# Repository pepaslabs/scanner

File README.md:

# Scanner

This ia a relay board for scanning voltage references.

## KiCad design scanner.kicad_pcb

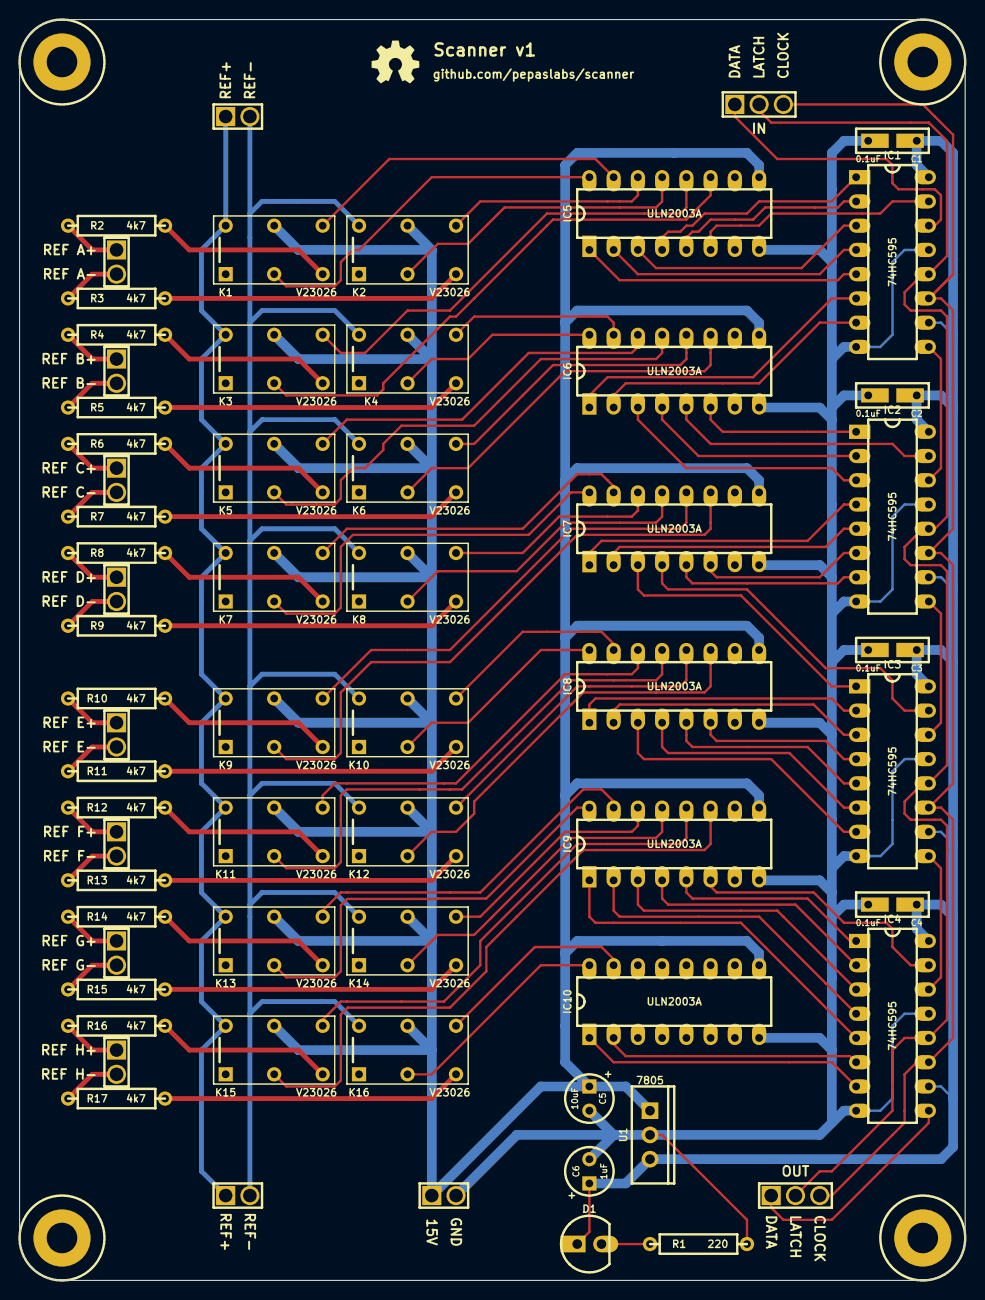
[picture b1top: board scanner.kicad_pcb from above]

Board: 2 copper layers, 99.1 x 132.1 mm, 68 parts (0 on the bottom side), 109 nets.

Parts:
C1, C2, C3, C4: 0.1uF; PL_ANYSSCAP_SMALL_2_059B_0805
C5: 10uF; PL_ELCAP_10_20_V_059A
C6: 1uF; PL_ELCAP_10_20_V_059A
D1: LED; PL_LED_5MM
H***: Val**; PL_hole_M3
H***#2, H***#3, H***#4: Val**; PL_hole_M3
IC1, IC2, IC3, IC4: 74HC595; PL_DIP16
IC5, IC6, IC7, IC8, IC9, IC10: ULN2003A; PL_DIP16
K1, K2, K3, K4, K5, K6, K7, K8, K9, K10, K11, K12, K13, K14, K15, K16: V23026; PL_V23026
P1, P3, P4, P5, P6, P7, P8, P9, P10, P11, P13: CONN_2X1; PL_SIL-2-MCHN
P2, P12: CONN_3X1; PL_SIL-3-MCHN
R1: 220; PL_R_AXIAL_0W25_059A
R2, R3, R4, R5, R6, R7, R8, R9, R10, R11, R12, R13, R14, R15, R16, R17: 4k7; PL_R_AXIAL_0W25_059A
U1: 7805; PL_TO-220_V_069A

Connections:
5V: C1.1, C2.1, C3.1, C4.1, C6.1, D1.1, IC1.10, IC1.16, IC2.10, IC2.16, IC3.10, IC3.16, IC4.10, IC4.16, U1.3
15V: C5.1, IC5.9, IC6.9, IC7.9, IC8.9, IC9.9, IC10.9, K1.5, K2.5, K3.5, K4.5, K5.5, K6.5, K7.5, K8.5, K9.5, K10.5, K11.5, K12.5, K13.5, K14.5, K15.5, K16.5, P1.1, U1.1
CLOCK: IC1.11, IC2.11, IC3.11, IC4.11, P2.3, P12.3
DATA: IC1.14, P2.1
DATA OUT: IC4.9, P12.1
GND: C1.2, C2.2, C3.2, C4.2, C5.2, C6.2, IC1.8, IC1.13, IC2.8, IC2.13, IC3.8, IC3.13, IC4.8, IC4.13, IC5.8, IC6.8, IC7.8, IC8.8, IC9.8, IC10.8, P1.2, R1.2, U1.2
LATCH: IC1.12, IC2.12, IC3.12, IC4.12, P2.2, P12.2
unnamed: IC8.16, K10.2
unnamed: IC7.13, K8.2
unnamed: IC7.12, K9.4
unnamed: IC7.14, K8.4
unnamed: IC8.15, K10.4
unnamed: IC8.14, K11.4
unnamed: IC8.13, K11.2
unnamed: IC8.12, K12.4
unnamed: IC6.16, K4.2
unnamed: IC6.15, K4.4
unnamed: IC6.14, K5.4
unnamed: IC6.13, K5.2
unnamed: IC6.12, K6.4
unnamed: IC7.16, K7.2
unnamed: IC7.15, K7.4
unnamed: IC9.12, K15.4
unnamed: IC9.16, K13.2
unnamed: IC9.15, K13.4
unnamed: IC9.14, K14.4
unnamed: IC10.16, K16.2
unnamed: IC10.15, K16.4
unnamed: IC5.14, K2.4
unnamed: IC5.16, K1.2
unnamed: IC5.15, K1.4
unnamed: IC5.13, K2.2
unnamed: IC5.12, K3.4
unnamed: P3.1, R2.1
unnamed: P3.2, R3.1
unnamed: D1.2, R1.1
unnamed: IC9.11, K15.2
unnamed: P4.1, R4.1
unnamed: P4.2, R5.1
unnamed: P5.1, R6.1
unnamed: P5.2, R7.1
unnamed: IC9.13, K14.2
unnamed: P6.1, R8.1
unnamed: P6.2, R9.1
unnamed: IC5.11, K3.2
unnamed: IC6.11, K6.2
unnamed: IC7.11, K9.2
unnamed: IC8.11, K12.2
unnamed: P9.1, R14.1
unnamed: P9.2, R15.1
unnamed: P10.1, R16.1
unnamed: P10.2, R17.1
unnamed: P8.2, R13.1
unnamed: P7.1, R10.1
unnamed: P7.2, R11.1
unnamed: P8.1, R12.1
unnamed: IC1.9, IC2.14
unnamed: IC2.9, IC3.14
unnamed: IC3.9, IC4.14
REF A+: K1.3, R2.2
REF A+ DIS: IC1.5, IC5.1
REF A+ EN: IC1.4, IC5.2
REF A-: K2.3, R3.2
REF A- DIS: IC1.1, IC5.4
REF A- EN: IC1.3, IC5.3
REF B+: K3.3, R4.2
REF B+ DIS: IC1.15, IC5.6
REF B+ EN: IC1.2, IC5.5
REF B-: K4.3, R5.2
REF B- DIS: IC1.6, IC6.1
REF B- EN: IC1.7, IC6.2
REF C+: K5.3, R6.2
REF C+ DIS: IC2.2, IC6.4
REF C+ EN: IC2.3, IC6.3
REF C-: K6.3, R7.2
REF C- DIS: IC2.1, IC6.6
REF C- EN: IC2.15, IC6.5
REF D+: K7.3, R8.2
REF D+ DIS: IC2.4, IC7.1
REF D+ EN: IC2.5, IC7.2
REF D-: K8.3, R9.2
REF D- DIS: IC3.15, IC7.4
REF D- EN: IC3.1, IC7.3
REF E+: K9.3, R10.2
REF E+ DIS: IC2.6, IC7.6
REF E+ EN: IC2.7, IC7.5
REF E-: K10.3, R11.2
REF E- DIS: IC3.2, IC8.1
REF E- EN: IC3.3, IC8.2
REF F+: K11.3, R12.2
REF F+ DIS: IC3.6, IC8.4
REF F+ EN: IC3.7, IC8.3
REF F-: K12.3, R13.2
REF F- DIS: IC3.4, IC8.6
REF F- EN: IC3.5, IC8.5
REF G+: K13.3, R14.2
REF G+ DIS: IC4.5, IC9.1
REF G+ EN: IC4.4, IC9.2
REF G-: K14.3, R15.2
REF G- DIS: IC4.2, IC9.4
REF G- EN: IC4.3, IC9.3
REF H+: K15.3, R16.2
REF H+ DIS: IC4.15, IC9.6
REF H+ EN: IC4.1, IC9.5
REF H-: K16.3, R17.2
REF H- DIS: IC4.7, IC10.1
REF H- EN: IC4.6, IC10.2
REF+: K1.6, K3.6, K5.6, K7.6, K9.6, K11.6, K13.6, K15.6, P11.1, P13.1
REF-: K2.6, K4.6, K6.6, K8.6, K10.6, K12.6, K14.6, K16.6, P11.2, P13.2

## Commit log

2022-09-05 initial import
